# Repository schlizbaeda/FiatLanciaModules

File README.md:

ACHTUNG:

Dieses Repository stammt weder vom Automobilhersteller "FIAT S.p.A.",
noch vom zum FIAT-Konzern gehörenden Automobilzulieferunternehmen 
"Magneti Marelli S.p.A."! Die Verwendung dieser Namen durch mich dient
lediglich der leichteren Zuordnung für den Leser, wofür die hier 
präsentierte Anleitung und weitere Daten dienen sollen.

# FiatLanciaModules
EPROM-Programmierung der Module für den Fiat/Lancia-Tester

In der Datei FL-Module_programmieren.pdf befindet sich eine Anleitung, wie 
aus vorhandenen EPROM-Modulen für den F/L-Tester aus den 90er-Jahren(?)
- die Moduldaten ausgelesen
- die Module (zum Widerbeschreiben) gelöscht 
- die Module neu programmiert

werden können.

Dieses GitHub-Repository enthält alle Dateien zur Erstellung dieser Doku-
mentation mittels LaTeX im Hauptverzeichnis sowie in den Unterverzeichnissen
Bilder, Kapitel und Layout

# Erstellung der pdf-Datei mittels LaTeX unter Ubuntu im Terminalfenster
$ sudo apt-get install texlive-full

$ pdflatex FL-Module_programmieren.tex

Während der Erstellung erscheint die Meldung

    l.180 \caption
                      {{\FLTester} und Memory}           
    ? 
mit blinkendem Cursor. Hier über die Tastatur R ENTER eingeben.

$ pdflatex FL-Module_programmieren.tex

Dieser zweite Aufruf ist in LaTeX erforderlich, um das Inhaltsverzeichnis
und die Verlinkungen des Dokumentes korrekt zu erstellen.

# Nachbau
Der Nachbau inkl. Schaltplänen ist in FL-Module_programmieren.pdf beschrieben.
Im Verzeichnis Hardware befinden sich weitere Informationen für den Nachbau:
- Layoutdaten für EAGLE
- IC-Datenblätter

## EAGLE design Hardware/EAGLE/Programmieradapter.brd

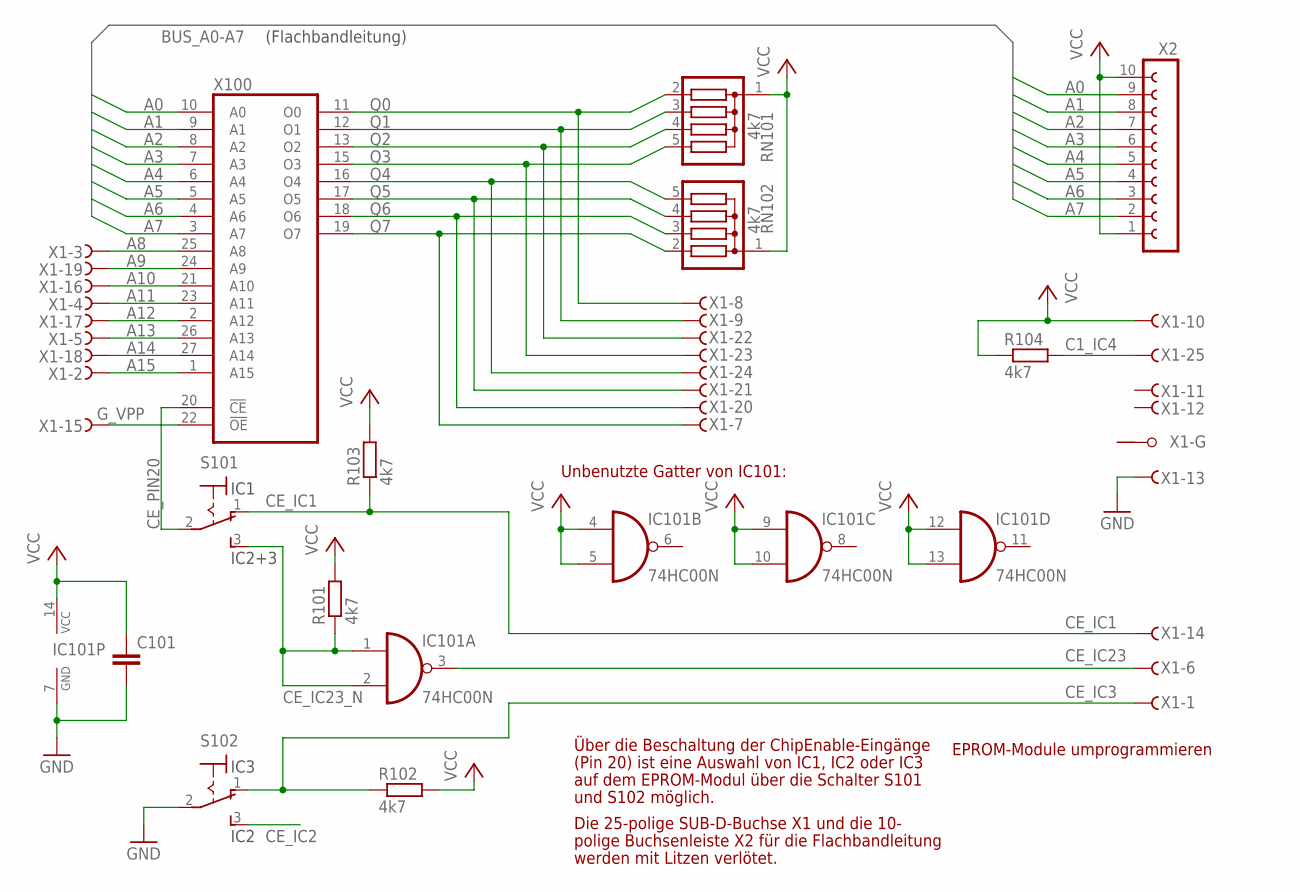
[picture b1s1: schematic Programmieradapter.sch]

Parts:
C101: C-EU050-024X044; C050-024X044
IC101: 74HC00N; DIL14
R101, R102, R103, R104: 4k7; 0207/10
RN101, RN102: 4k7; SIL5
S101, S102: 320-916
X1: F25VPS; F25VP
X2: FE10-1; FE10
X100: 27512; DIL28

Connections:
A0: X2.9, X100.10 (A0)
A1: X2.8, X100.9 (A1)
A2: X2.7, X100.8 (A2)
A3: X2.6, X100.7 (A3)
A4: X2.5, X100.6 (A4)
A5: X2.4, X100.5 (A5)
A6: X2.3, X100.4 (A6)
A7: X2.2, X100.3 (A7)
A8: X1.3 (F), X100.25 (A8)
A9: X1.19 (F), X100.24 (A9)
A10: X1.16 (F), X100.21 (A10)
A11: X1.4 (F), X100.23 (A11)
A12: X1.17 (F), X100.2 (A12)
A13: X1.5 (F), X100.26 (A13)
A14: X1.18 (F), X100.27 (A14)
A15: X1.2 (F), X100.1 (A15)
C1_IC4: R104.2, X1.25 (F)
CE_IC1: R103.1, S101.1 (O), X1.14 (F)
CE_IC2: S102.3 (S)
CE_IC3: R102.1, S102.1 (O), X1.1 (F)
CE_IC23: IC101.3 (O), X1.6 (F)
CE_IC23_N: IC101.1 (I0), IC101.2 (I1), R101.1, S101.3 (S)
CE_PIN20: S101.2, X100.20 (!CE)
GND: C101.2, IC101.7 (GND), S102.2, X1.13 (F), X100.14 (GND)
G_VPP: X1.15 (F), X100.22 (!OE)
Q0: RN101.2, X1.8 (F), X100.11 (O0)
Q1: RN101.3, X1.9 (F), X100.12 (O1)
Q2: RN101.4, X1.22 (F), X100.13 (O2)
Q3: RN101.5, X1.23 (F), X100.15 (O3)
Q4: RN102.5, X1.24 (F), X100.16 (O4)
Q5: RN102.4, X1.21 (F), X100.17 (O5)
Q6: RN102.3, X1.20 (F), X100.18 (O6)
Q7: RN102.2, X1.7 (F), X100.19 (O7)
VCC: C101.1, IC101.4 (I0), IC101.5 (I1), IC101.9 (I0), IC101.10 (I1), IC101.12 (I0), IC101.13 (I1), IC101.14 (VCC), R101.2, R102.2, R103.2, R104.1, RN101.1, RN102.1, X1.10 (F), X2.1, X2.10, X100.28 (VCC)

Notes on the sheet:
IC1
IC2+3
IC2
IC3
Über die Beschaltung der ChipEnable-Eingänge
(Pin 20) ist eine Auswahl von IC1, IC2 oder IC3
auf dem EPROM-Modul über die Schalter S101
und S102 möglich.
EPROM-Module umprogrammieren
Unbenutzte Gatter von IC101:
(Flachbandleitung)
Die 25-polige SUB-D-Buchse X1 und die 10-
polige Buchsenleiste X2 für die Flachbandleitung
werden mit Litzen verlötet.

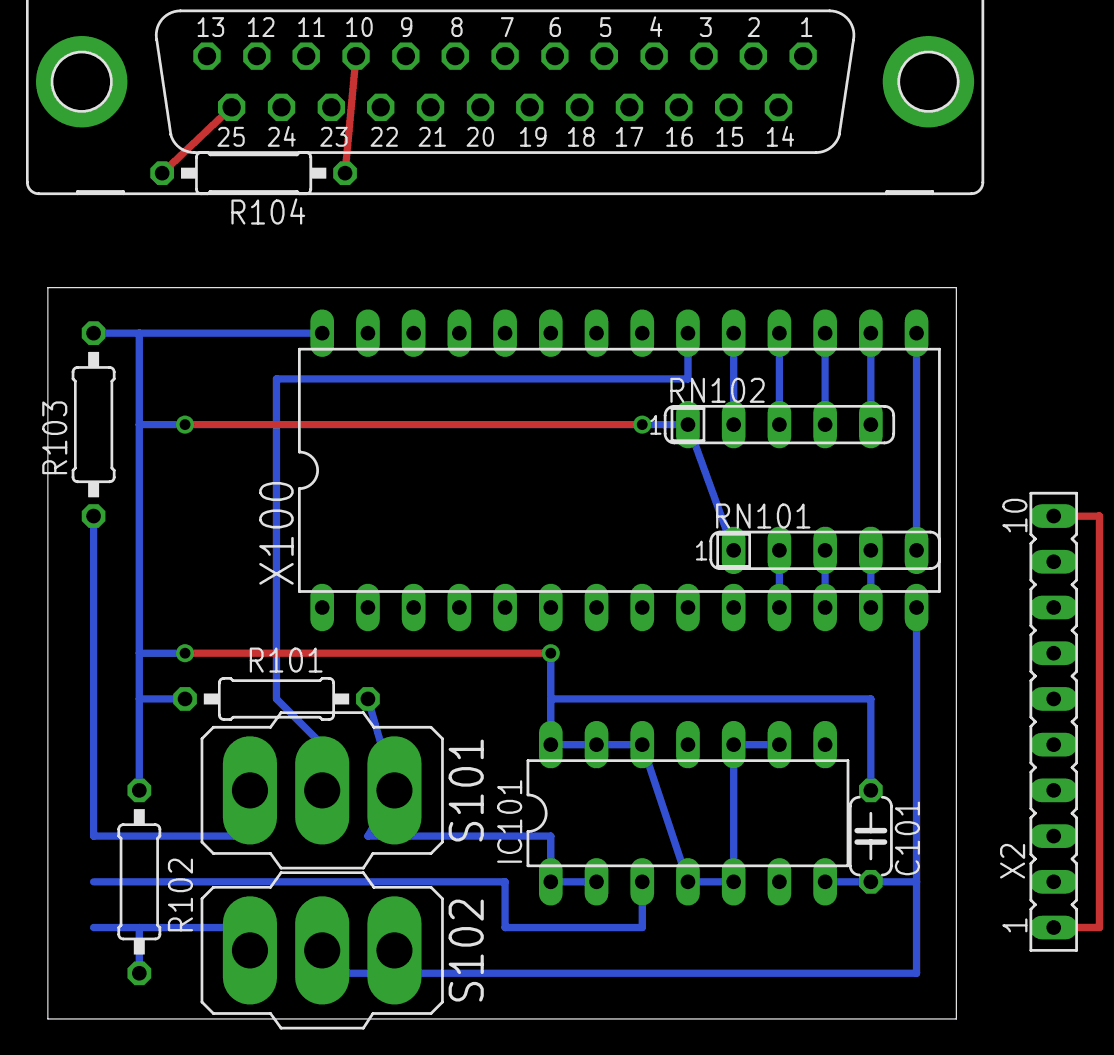
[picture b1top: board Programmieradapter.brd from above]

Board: 2 copper layers, 50.5 x 40.6 mm, 13 parts (0 on the bottom side), 33 nets.

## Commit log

2017-05-16 Add files via upload
    "kastrierte" Anleitung, bis die rechtlichen Punkte geklärt sind
2018-06-09 Create LICENSE
